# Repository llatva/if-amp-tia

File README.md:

# if-amp-tia
Termination insensitive IF amplifier board (two independent UNIdirectional amplifiers on single board)
Powering: +12V regulated input.

PCB layout by Lasse OH3HZB (2022), based on work by Jan OM2ATC.
Original design by Wes Hayward W7ZOI and Bob Kopski K3NHI.

THE CONTENTS IN THIS REPOSITORY IS PROVIDED "AS IS", WITHOUT WARRANTY OF ANY KIND, 
EXPRESS OR IMPLIED, INCLUDING BUT NOT LIMITED TO THE WARRANTIES OF MERCHANTABILITY,
FITNESS FOR A PARTICULAR PURPOSE AND NONINFRINGEMENT. IN NO EVENT SHALL THE
AUTHORS OR COPYRIGHT HOLDERS BE LIABLE FOR ANY CLAIM, DAMAGES OR OTHER
LIABILITY, WHETHER IN AN ACTION OF CONTRACT, TORT OR OTHERWISE, ARISING FROM,
OUT OF OR IN CONNECTION WITH THE SOFTWARE OR THE USE OR OTHER DEALINGS IN THE
SOFTWARE.

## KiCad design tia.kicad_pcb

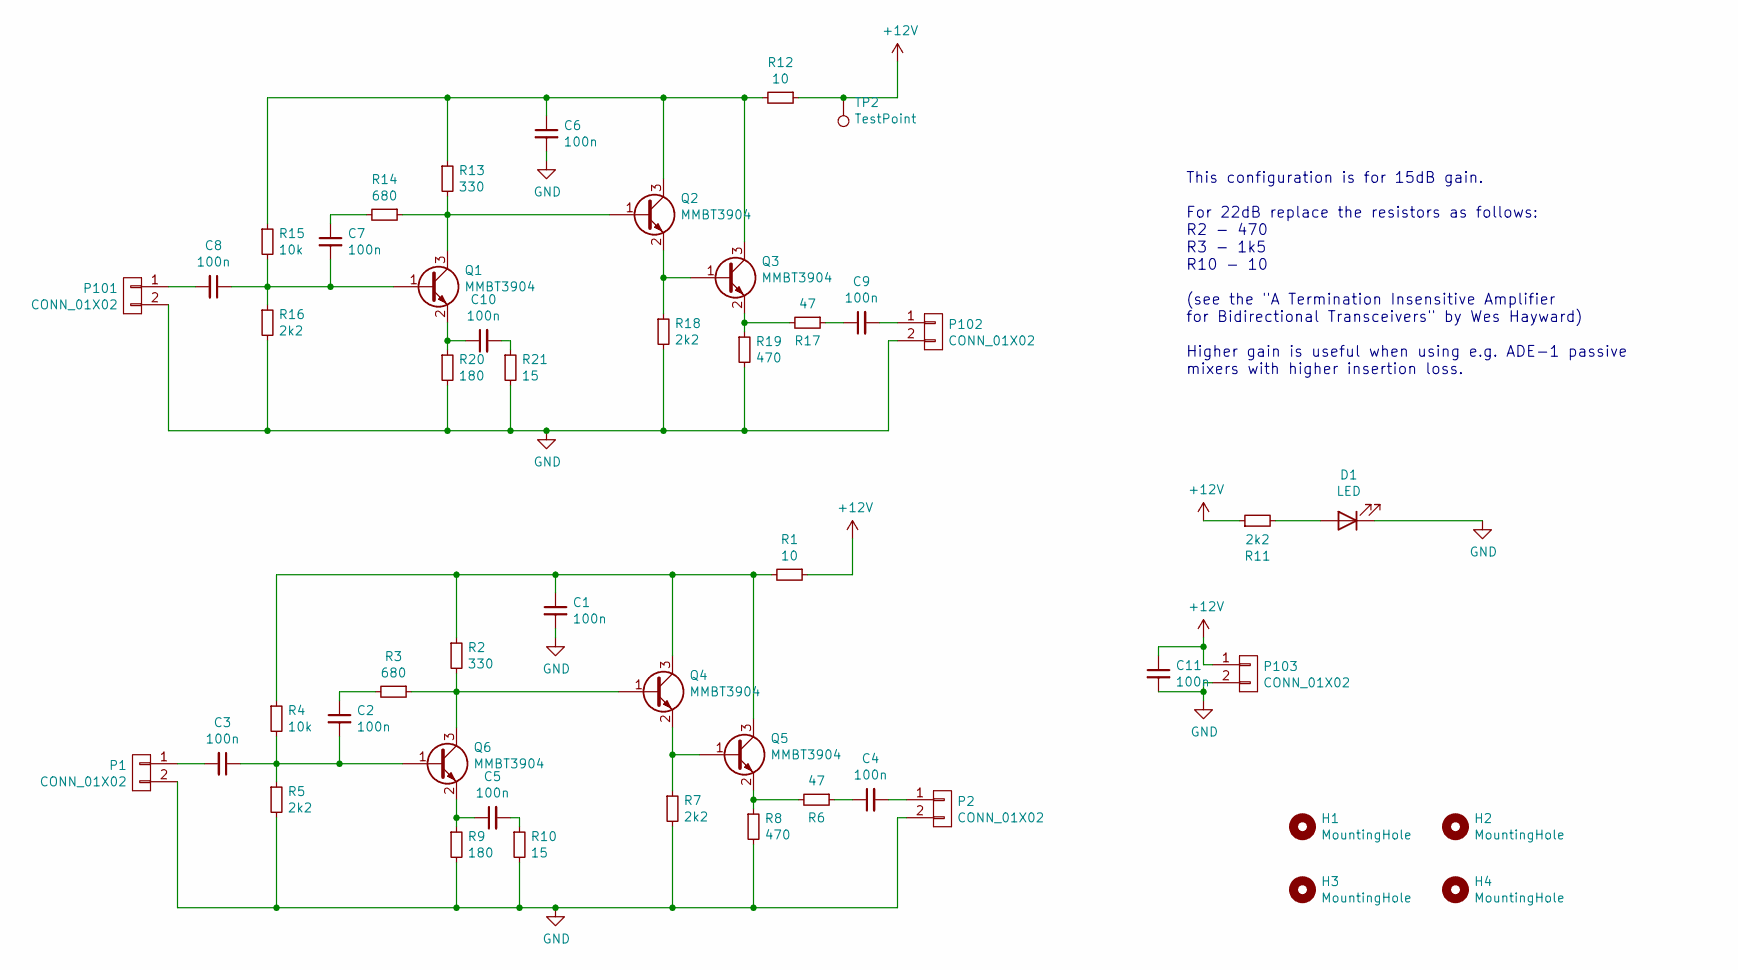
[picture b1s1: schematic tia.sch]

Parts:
C1, C2, C3, C4, C5, C6, C7, C8, C9, C10, C11: 100n; C_0805_2012Metric_Pad1.18x1.45mm_HandSolder; JLCPART C49678
D1: LED; LED_0805_2012Metric_Pad1.15x1.40mm_HandSolder; JLCPART C2297
H1, H2, H3, H4: MountingHole; MountingHole_2.5mm_Pad
P1, P2, P101, P102, P103: CONN_01X02; PinHeader_1x02_P2.54mm_Vertical
Q1, Q2, Q3, Q4, Q5, Q6: MMBT3904; SOT-23; JLCPART C20526
R1, R12: 10; R_0603_1608Metric_Pad0.98x0.95mm_HandSolder; JLCPART C22859
R2, R13: 330; R_0603_1608Metric_Pad0.98x0.95mm_HandSolder; JLCPART C23138
R3, R14: 680; R_0603_1608Metric_Pad0.98x0.95mm_HandSolder; JLCPART C23228
R4, R15: 10k; R_0603_1608Metric_Pad0.98x0.95mm_HandSolder; JLCPART C25804
R5, R7, R11, R16, R18: 2k2; R_0603_1608Metric_Pad0.98x0.95mm_HandSolder; JLCPART C4190
R6, R17: 47; R_0603_1608Metric_Pad0.98x0.95mm_HandSolder; JLCPART C23182
R8, R19: 470; R_0603_1608Metric_Pad0.98x0.95mm_HandSolder; JLCPART C23179
R9, R20: 180; R_0603_1608Metric_Pad0.98x0.95mm_HandSolder; JLCPART C22828
R10, R21: 15; R_0603_1608Metric_Pad0.98x0.95mm_HandSolder; JLCPART C22810
TP2: TestPoint; TestPoint_Pad_D1.0mm

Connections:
+12V: C11.1, P103.1, R1.1, R11.1, R12.1, TP2.1
GND: C1.2, C6.2, C11.2, D1.1 (K), P1.2, P2.2, P101.2, P102.2, P103.2, R5.2, R7.2, R8.2, R9.2, R10.2, R16.2, R18.2, R19.2, R20.2, R21.2
unnamed: C1.1, Q4.3 (C), Q5.3 (C), R1.2, R2.1, R4.1
unnamed: C2.1, R3.2
unnamed: C2.2, C3.1, Q6.1 (B), R4.2, R5.1
unnamed: C3.2, P1.1
unnamed: C4.1, R6.1
unnamed: C4.2, P2.1
unnamed: C5.1, Q6.2 (E), R9.1
unnamed: C5.2, R10.1
unnamed: C6.1, Q2.3 (C), Q3.3 (C), R12.2, R13.1, R15.1
unnamed: C7.1, R14.2
unnamed: C7.2, C8.1, Q1.1 (B), R15.2, R16.1
unnamed: C8.2, P101.1
unnamed: C9.1, R17.1
unnamed: C9.2, P102.1
unnamed: C10.1, Q1.2 (E), R20.1
unnamed: C10.2, R21.1
unnamed: D1.2 (A), R11.2
unnamed: Q1.3 (C), Q2.1 (B), R13.2, R14.1
unnamed: Q2.2 (E), Q3.1 (B), R18.1
unnamed: Q3.2 (E), R17.2, R19.1
unnamed: Q4.1 (B), Q6.3 (C), R2.2, R3.1
unnamed: Q4.2 (E), Q5.1 (B), R7.1
unnamed: Q5.2 (E), R6.2, R8.1

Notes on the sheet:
This configuration is for 15dB gain. For 22dB replace the resistors as follows: R2 - 470 R3 - 1k5 R10 - 10 (see the "A Termination Insensitive Amplifier for Bidirectional Transceivers" by Wes Hayward) Higher gain is useful when using e.g. ADE-1 passive mixers with higher insertion loss.

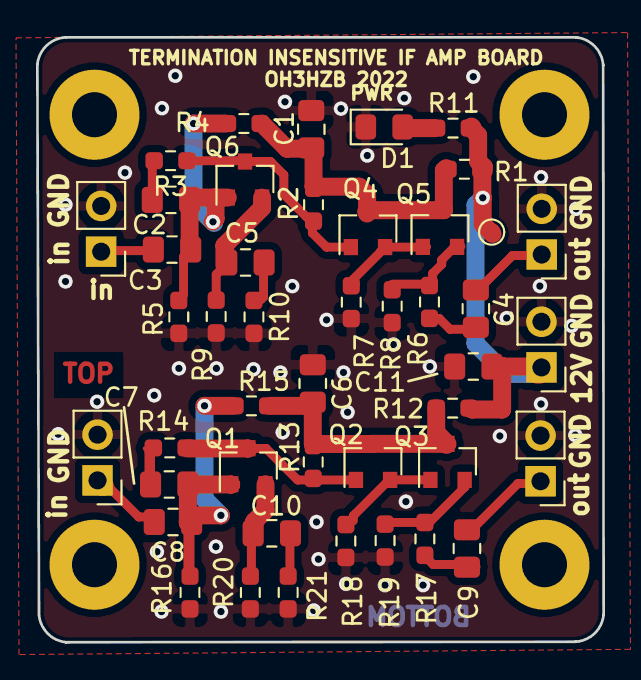
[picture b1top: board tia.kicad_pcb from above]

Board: 2 copper layers, 31.5 x 33.6 mm, 49 parts (0 on the bottom side), 25 nets.

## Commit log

2022-01-15 initial commit to Github
2022-01-15 deleted backup directory
2022-01-15 Add files via upload
    preview images
2022-01-15 removed smt dir
2022-03-12 schematic as PDF
